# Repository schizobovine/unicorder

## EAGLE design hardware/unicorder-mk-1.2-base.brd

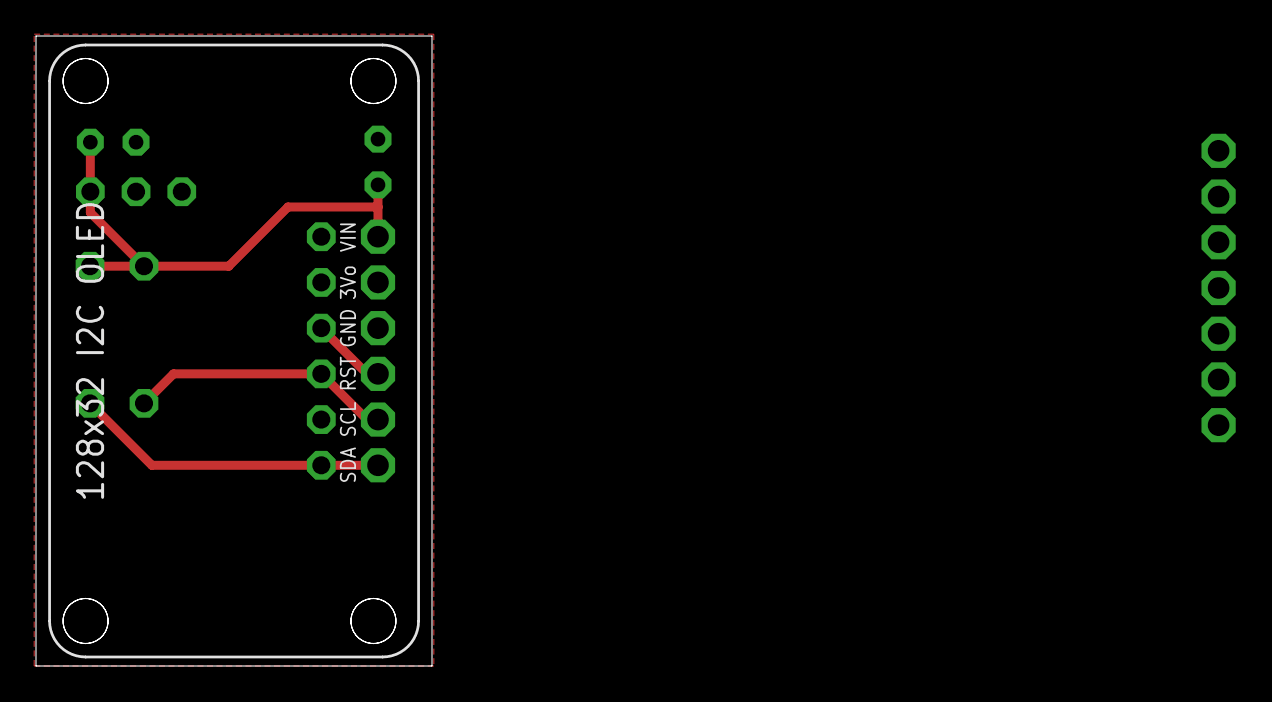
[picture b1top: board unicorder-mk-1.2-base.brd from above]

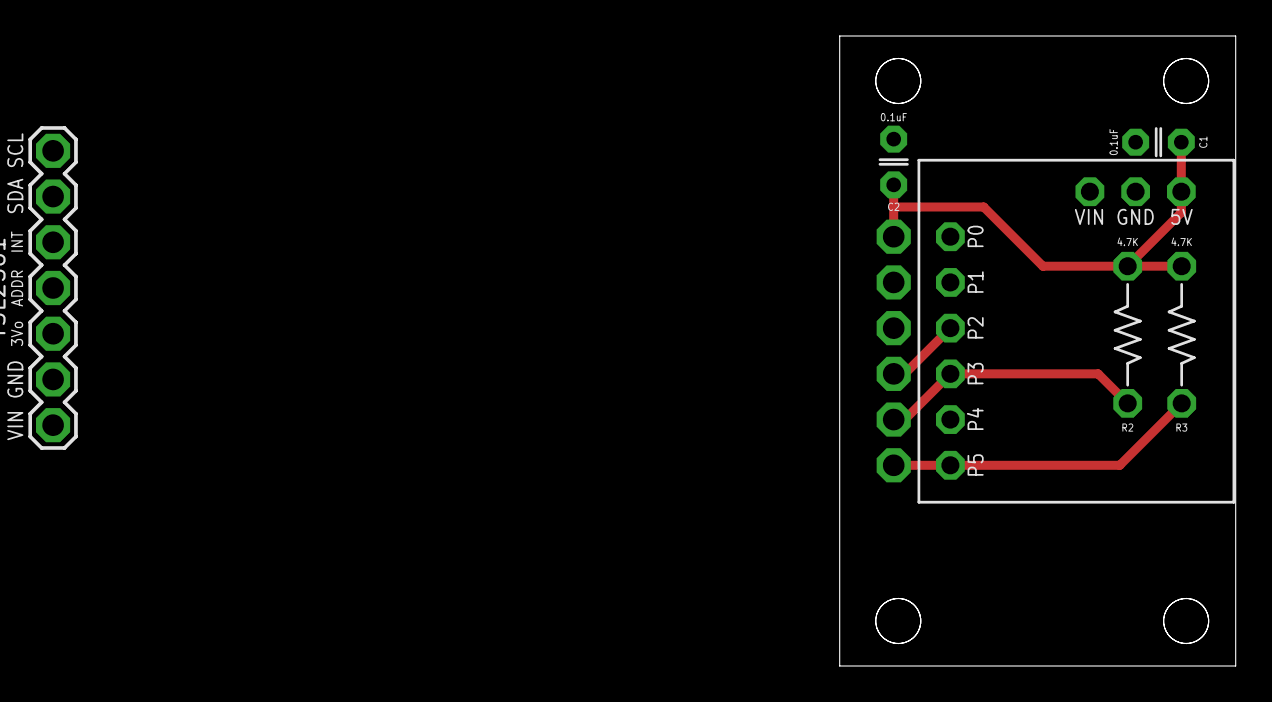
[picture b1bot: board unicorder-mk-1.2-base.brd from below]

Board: 2 copper layers, 22.0 x 35.0 mm, 8 parts (6 on the bottom side), 5 nets.

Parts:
C1, C2: 0.1uF; C025-024X044
DISPLAY1: ADAFRUIT_128X32_OLED_I2CCLOSER; ADAFRUIT_128X32_OLED_I2C_CLOSER
FRAME1: DUMMY
R2, R3: 4.7K; RESISTOR-AXIAL-PTH-7.62MM
TSL2561: 1X07_PTH_SLIMASS
U1: DIGISPARK_SHIELD

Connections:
DISPLAY_RST: DISPLAY1.RST, U1.P3
GND: C1.2, C2.2, DISPLAY1.GND, TSL2561.6, U1.GND
MOSI/SDA: DISPLAY1.SDA, R3.P$1, TSL2561.2, U1.P0
SCK/SCL: DISPLAY1.SCL, R2.P$1, TSL2561.1, U1.P2
VCC: C1.1, C2.1, DISPLAY1.VIN, R2.P$2, R3.P$2, TSL2561.7, U1.5V

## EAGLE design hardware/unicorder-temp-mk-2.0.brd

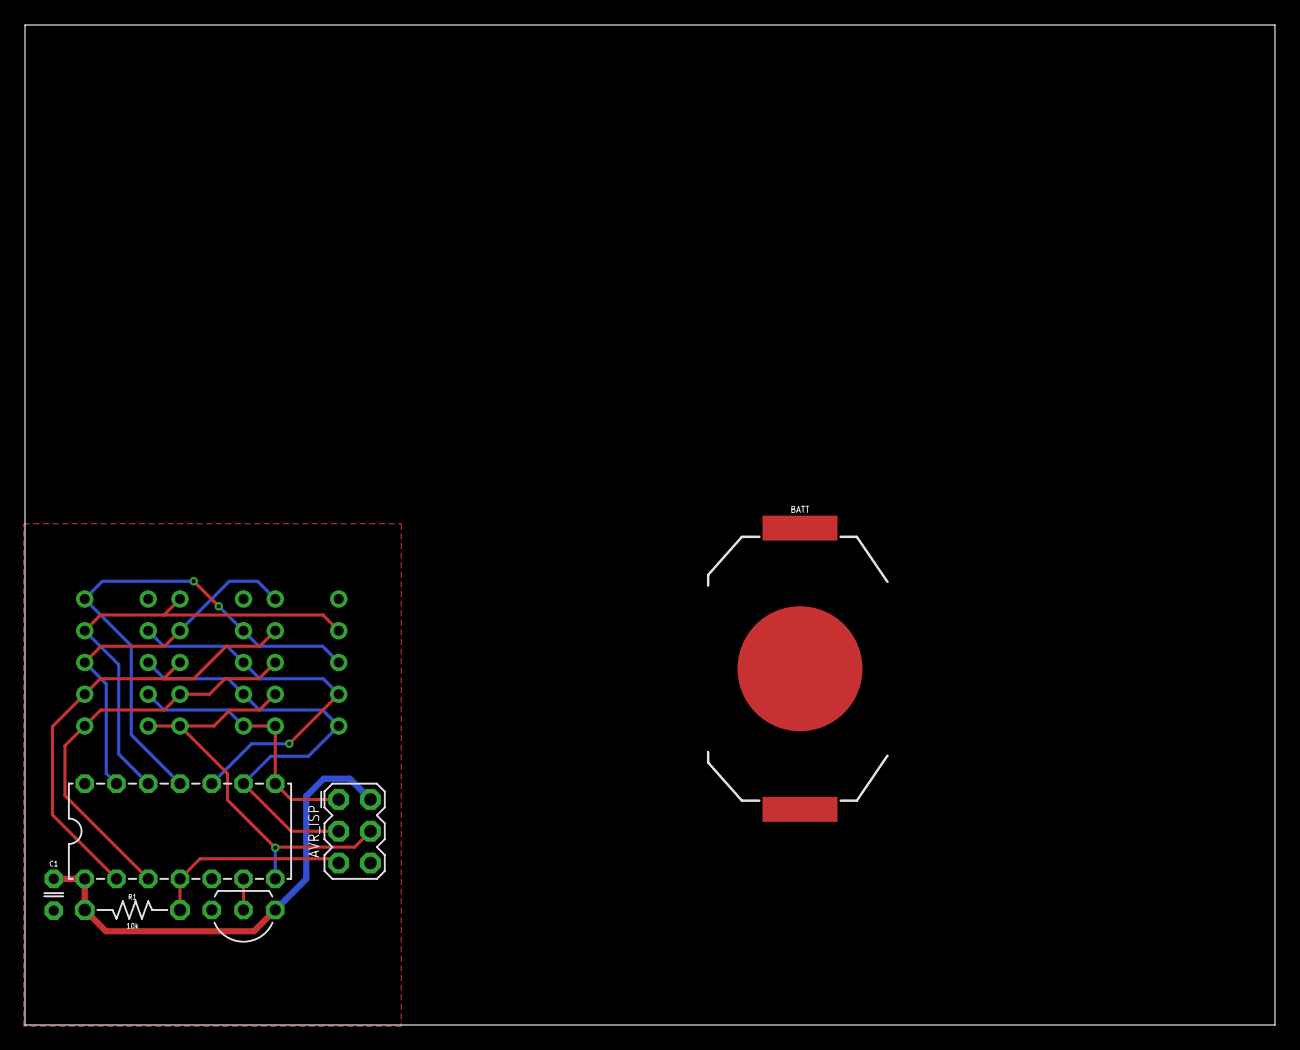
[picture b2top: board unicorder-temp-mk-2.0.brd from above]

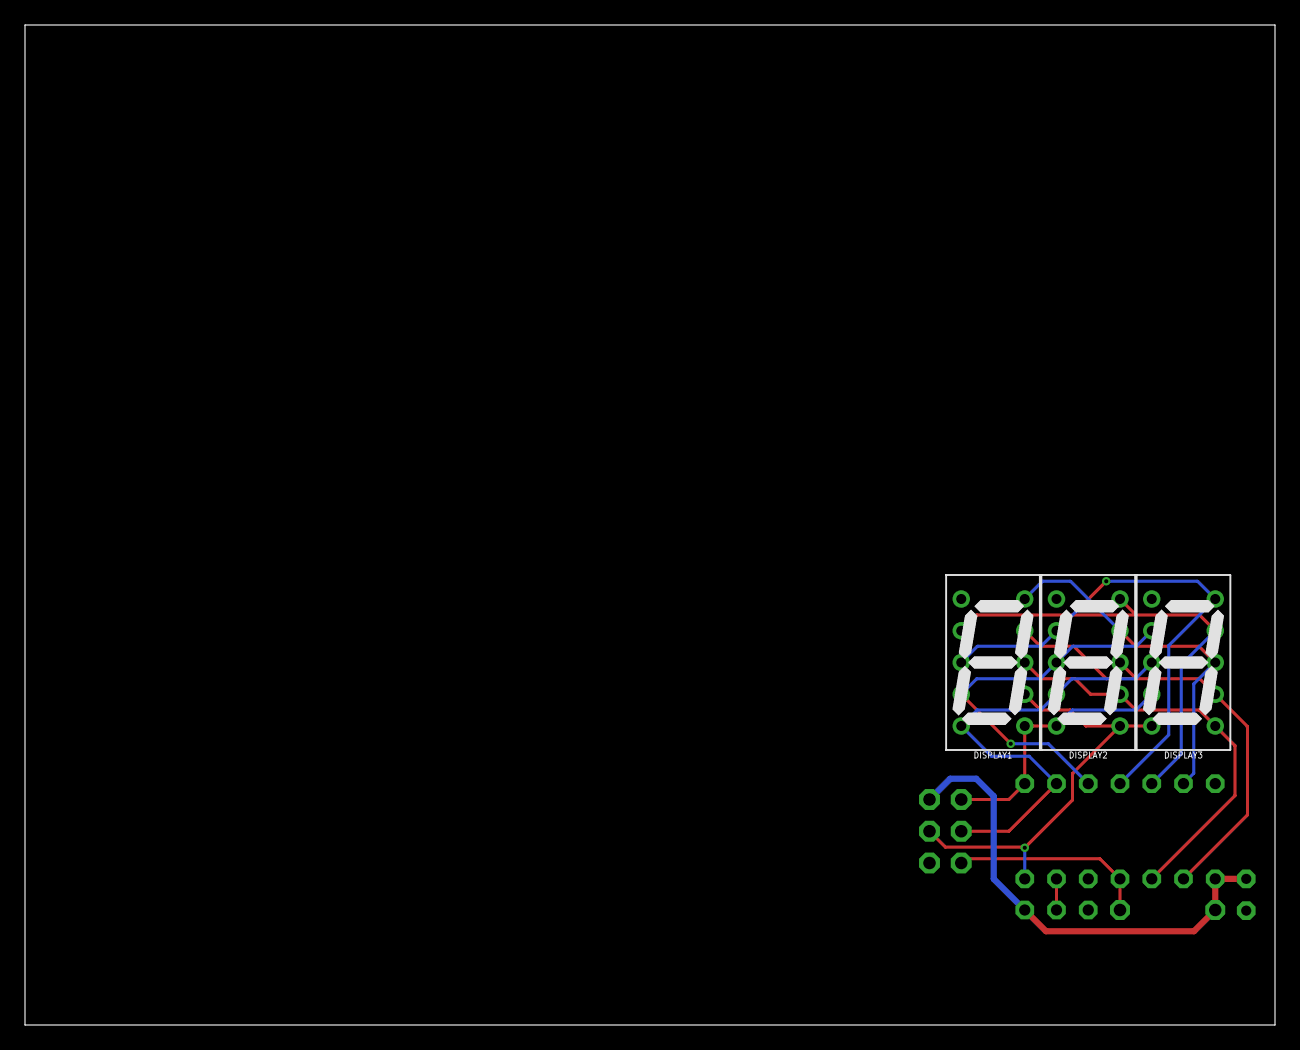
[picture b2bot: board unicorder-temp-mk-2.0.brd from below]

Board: 2 copper layers, 100.0 x 80.0 mm, 10 parts (3 on the bottom side), 13 nets.

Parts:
AVR_ISP: AVR_SPI_PRG_6PTH; 2X3
BATT: CR2032; BATTCON_20MM_MINE
C1: 0.1uF; C025-024X044
DISPLAY1, DISPLAY2, DISPLAY3: 7SEG_1DIG-2; 7SEG_1DIG_10MM
FRAME1: DUMMY
IC1: ATTINY84; DIL14
IC2: TMP36; TO-92-AMMO
R1: 10k; RESISTOR-AXIAL-PTH-7.62MM

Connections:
ADC7: IC1.6, IC2.2
GND: AVR_ISP.6, BATT.BOTTOM, C1.2, IC1.14, IC2.3
PA0: DISPLAY1.10, DISPLAY2.9, DISPLAY3.8, IC1.13
PA1: DISPLAY1.2, DISPLAY2.10, DISPLAY3.9, IC1.12
PA2: DISPLAY1.3, DISPLAY2.2, DISPLAY3.10, IC1.11
PA3: DISPLAY1.4, DISPLAY2.3, DISPLAY3.2, IC1.10
PA4: AVR_ISP.3, DISPLAY1.5, DISPLAY2.4, DISPLAY3.3, IC1.9
PA5: AVR_ISP.1, DISPLAY1.6, DISPLAY2.5, DISPLAY3.4, IC1.8
PA6: AVR_ISP.4, DISPLAY1.7, DISPLAY2.6, DISPLAY3.5, IC1.7
PB0: DISPLAY1.9, DISPLAY2.8, DISPLAY3.7, IC1.2
PB1: DISPLAY1.8, DISPLAY2.7, DISPLAY3.6, IC1.3
RST: AVR_ISP.5, IC1.4, R1.P$1
VCC: AVR_ISP.2, BATT.TOP@1, C1.1, IC1.1, IC2.1, R1.P$2
